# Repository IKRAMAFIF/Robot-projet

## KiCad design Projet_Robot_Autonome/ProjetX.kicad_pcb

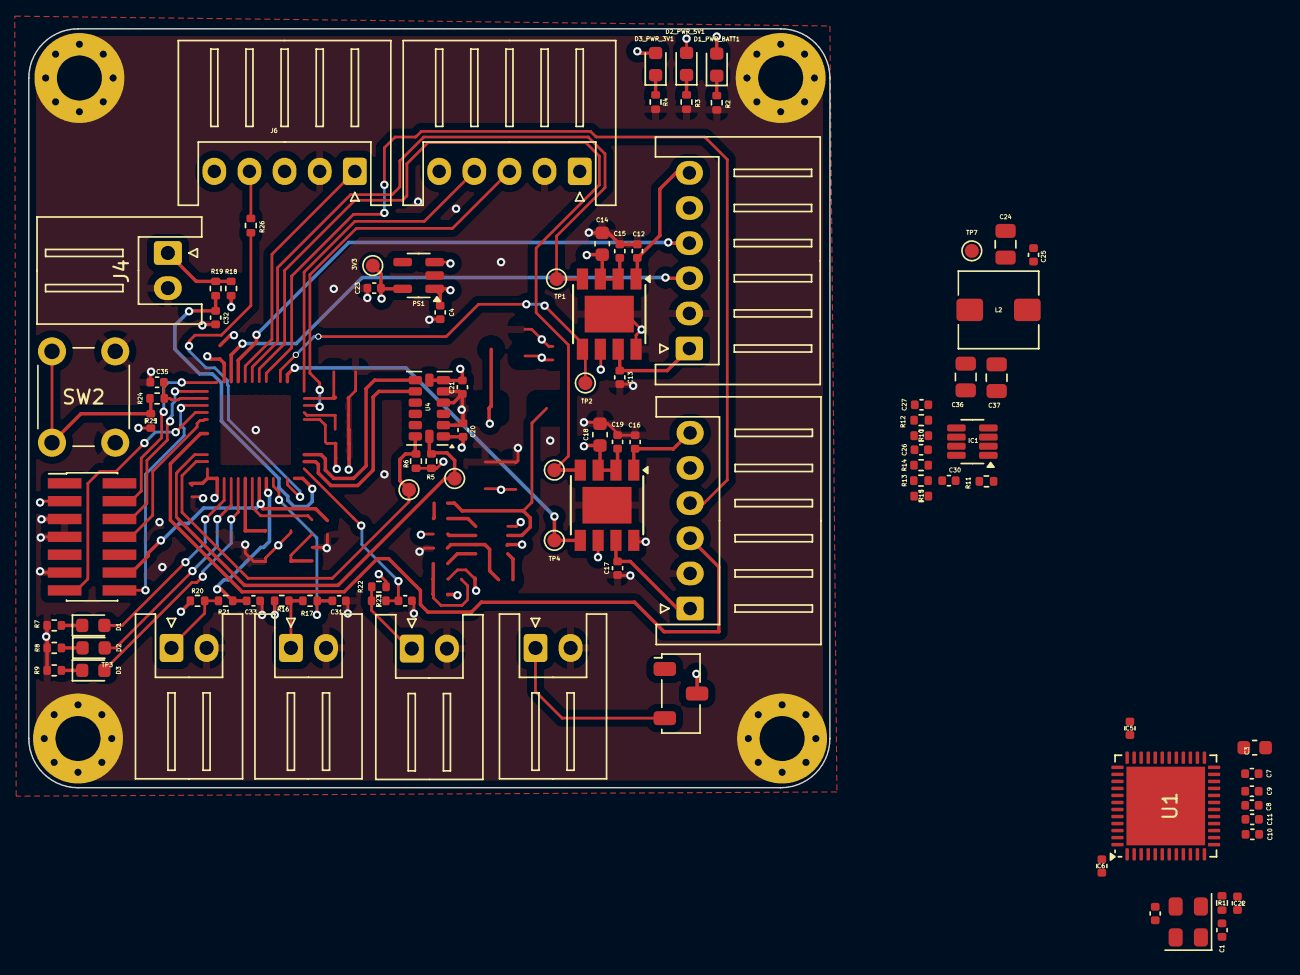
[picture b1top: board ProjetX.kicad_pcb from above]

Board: 4 copper layers, 57.0 x 54.0 mm, 99 parts (0 on the bottom side), 62 nets.

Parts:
3V3: TestPoint; TestPoint_Pad_D1.0mm
C1, C2: 10p; C_0402_1005Metric
C3: 4.7uF; C_0603_1608Metric
C4: 0.47u; C_0402_1005Metric
C5, C6, C7, C11, C12, C13, C16, C17, C22, C35: 100n; C_0402_1005Metric
C8, C31, C32, C33, C34: 10n; C_0402_1005Metric
C9, C10, C15, C19: 1u; C_0402_1005Metric
C14, C18: 10u; C_0603_1608Metric
C20, C23: 1uF; C_0402_1005Metric
C21, C25, C26: 100nF; C_0402_1005Metric
C24, C36, C37: 22uF; C_0805_2012Metric
C27: 100uF; C_0402_1005Metric
C30: 15pF; C_0402_1005Metric
D1, D1_PWR_BATT1, D2, D2_PWR_5V1, D3, D3_PWR_3V1: LED; LED_0603_1608Metric
H1, H2, H3, H4: MountingHole_Pad; MountingHole_3.2mm_M3_Pad_Via
IC1: MP1475DJ-LF-P; TSOT-23-8
J1: Conn_ST_STDC14; PinHeader_2x07_P1.27mm_Vertical_SMD
J2: Screw_Terminal_01x02; JST_XH_S2B-XH-A_1x02_P2.50mm_Horizontal
J3, J5: Conn_01x06; JST_XH_S6B-XH-A_1x06_P2.50mm_Horizontal
J4, J7, J8, J9: BORDER; JST_XH_S2B-XH-A_1x02_P2.50mm_Horizontal
J6, J11: Conn_01x05; JST_XH_S5B-XH-A_1x05_P2.50mm_Horizontal
L2: 4.7uH; L_Wuerth_HCI-5040
PS1: BU33SD5WG-TR; TSOT-23-5
R1: 10; R_0402_1005Metric
R2: 5k5; R_0402_1005Metric
R3: 3k3; R_0402_1005Metric
R4, R7, R8, R9: 1k6; R_0402_1005Metric
R5, R6, R24, R25: 1k; R_0402_1005Metric
R10, R11: 100k; R_0402_1005Metric
R12: 20R; R_0402_1005Metric
R13: 40.2k; R_0402_1005Metric
R14: 16k; R_0402_1005Metric
R15: 7.68k; R_0402_1005Metric
R16, R17, R18, R19, R20, R21, R22, R23: 10k; R_0402_1005Metric
R26: 470R; R_0402_1005Metric
SW1: ON/OFF; Nidec_Copal_CAS-120A
SW2: SW_Push; SW_PUSH_6mm_H9.5mm
TP1, TP2, TP3, TP4, TP5, TP6, TP7: TestPoint; TestPoint_Pad_D1.0mm
U1: STM32G431CBUx; QFN-48-1EP_7x7mm_P0.5mm_EP5.6x5.6mm
U2, U3: ZXBM5210-SP; Diodes_SO-8EP
U4: ADXL343; LGA-14_3x5mm_P0.8mm_LayoutBorder1x6y
Y1: Crystal_GND24_Small; Crystal_SMD_EuroQuartz_MT-4Pin_3.2x2.5mm

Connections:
+3.3V: 3V3.1, C3.2, C5.2, C6.2, C7.2, C8.2, C9.2, C10.2, C11.2, C20.2, C21.2, C23.1, D3_PWR_3V1.2 (A), J1.3 (VCC), J3.5, J5.5, PS1.5 (VOUT), R5.2, R6.2, R16.1, R18.1, R20.1, R22.1, R25.2, U1.1 (VBAT), U1.20 (VREF+), U1.21 (VDDA), U1.23 (VDD), U1.35 (VDD), U1.48 (VDD), U4.1 (Vdd_I/O), U4.6 (Vs), U4.7 (~CS)
+5V: C4.1, C30.2, C36.1, C37.1, D2_PWR_5V1.2 (A), J6.5, J11.5, L2.2, PS1.1 (VIN), PS1.3 (STBY), R13.2, TP7.1
+BATT: C14.1, C15.1, C18.1, C19.1, C24.1, C25.1, D1_PWR_BATT1.2 (A), IC1.2 (IN), R10.1, SW1.2 (B), U2.2 (VM), U2.3 (VDD), U2.6 (VREF), U3.2 (VM), U3.3 (VDD), U3.6 (VREF)
/Actionneurs/ENCOD_A1: J3.3, U1.34 (PA12)
/Actionneurs/ENCOD_A2: J5.3, U1.43 (PB5)
/Actionneurs/ENCOD_B1: J3.4, U1.33 (PA11)
/Actionneurs/ENCOD_B2: J5.4, U1.29 (PC6)
/Actionneurs/FWD1: TP1.1, U1.31 (PA9), U2.4 (FWD)
/Actionneurs/FWD2: TP3.1, U1.30 (PA8), U3.4 (FWD)
/Actionneurs/MOTEUR1+: C12.2, J3.6, U2.1 (OUT1)
/Actionneurs/MOTEUR1-: C13.1, J3.1, U2.7 (OUT2)
/Actionneurs/MOTEUR2+: C16.2, J5.6, U3.1 (OUT1)
/Actionneurs/MOTEUR2-: C17.1, J5.1, U3.7 (OUT2)
/Actionneurs/REV1: TP2.1, U1.27 (PB14), U2.5 (REV)
/Actionneurs/REV2: TP4.1, U1.26 (PB13), U3.5 (REV)
/STM32/BLE_RX: J11.3, U1.22 (PB10)
/STM32/BLE_TX: J11.4, U1.24 (PB11)
/STM32/BORDER_1: C33.1, R21.2, U1.8 (PA0)
/STM32/BORDER_2: C31.1, R17.2, U1.9 (PA1)
/STM32/BORDER_3: C34.1, R23.2, U1.13 (PA5)
/STM32/BORDER_4: C32.1, R19.2, U1.12 (PA4)
/STM32/CHAT/SOURIS: C35.1, R24.1, U1.38 (PA15)
/STM32/INT1_ACC: U1.15 (PA7), U4.8 (INT1)
/STM32/INT2_ACC: U1.14 (PA6), U4.9 (INT2)
/STM32/LD_ST1: D1.2 (A), U1.2 (PC13)
/STM32/LD_ST2: D2.2 (A), U1.3 (PC14)
/STM32/LD_ST3: D3.2 (A), U1.4 (PC15)
/STM32/LIDAR_M_CTR: J6.1, U1.32 (PA10)
/STM32/LIDAR_TX: R26.2, U1.11 (PA3)
/STM32/NRST: C22.2, J1.12 (~RST), U1.7 (PG10)
/STM32/RX_SWD: J1.13 (VCP_RX), U1.40 (PC11)
/STM32/SCL: R5.1, TP6.1, U1.46 (PB8), U4.14 (SCL/SCLK)
/STM32/SDA: R6.1, TP5.1, U1.47 (PB9), U4.13 (SDA/SDI/SDIO)
/STM32/SWCLK: J1.6 (JCLK/SWCLK), U1.37 (PA14)
/STM32/SWDIO: J1.4 (JTMS/SWDIO), U1.36 (PA13)
/STM32/SWO: J1.8 (JTDO/SWO), U1.41 (PB3)
/STM32/TX_SWD: J1.14 (VCP_TX), U1.39 (PC10)
GND: C1.1, C2.2, C3.1, C4.2, C5.1, C6.1, C7.1, C8.1, C9.1, C10.1, C11.1, C12.1, C13.2, C14.2, C15.2, C16.1, C17.2, C18.2, C19.2, C20.1, C21.1, C22.1, C23.2, C24.2, C25.2, C26.2, C31.2, C32.2, C33.2, C34.2, C35.2, C36.2, C37.2, H1.1, H2.1, H3.1, H4.1, IC1.4 (GND), J1.5 (GND), J1.7 (GND), J1.11 (GNDDetect), J2.2, J3.2, J4.2, J5.2, J6.2, J7.2, J8.2, J9.2, J11.2, PS1.2 (GND), R2.2, R3.2, R4.2, R7.2, R8.2, R9.2, R15.1, SW2.2, U1.49 (VSS), U2.8 (GND), U2.9 (GND), U3.8 (GND), U3.9 (GND), U4.2 (GND), U4.4 (GND), U4.5 (GND), Y1.2, Y1.4
unnamed: C1.2, R1.1, Y1.1
unnamed: C27.1, R12.2
unnamed: C30.1, R13.1, R14.2, R15.2
unnamed: D1.1 (K), R7.1
unnamed: D1_PWR_BATT1.1 (K), R2.1
unnamed: D2.1 (K), R8.1
unnamed: D2_PWR_5V1.1 (K), R3.1
unnamed: D3.1 (K), R9.1
unnamed: D3_PWR_3V1.1 (K), R4.1
unnamed: IC1.5 (BST), R12.1
unnamed: IC1.6 (EN/SYNC), R10.2
unnamed: IC1.8 (FB), R14.1
unnamed: IC1.1 (PG), R11.2
unnamed: C27.2, IC1.3 (SW), L2.1
unnamed: C26.1, IC1.7 (VCC), R11.1
unnamed: J2.1, SW1.3 (A)
unnamed: J4.1, R18.2, R19.1
unnamed: J6.4, R26.1
unnamed: J7.1, R16.2, R17.1
unnamed: J8.1, R20.2, R21.1
unnamed: J9.1, R22.2, R23.1
unnamed: R24.2, R25.1, SW2.1
unnamed: C2.1, U1.5 (PF0), Y1.3
unnamed: R1.2, U1.6 (PF1)

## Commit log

2025-10-07 show errors
